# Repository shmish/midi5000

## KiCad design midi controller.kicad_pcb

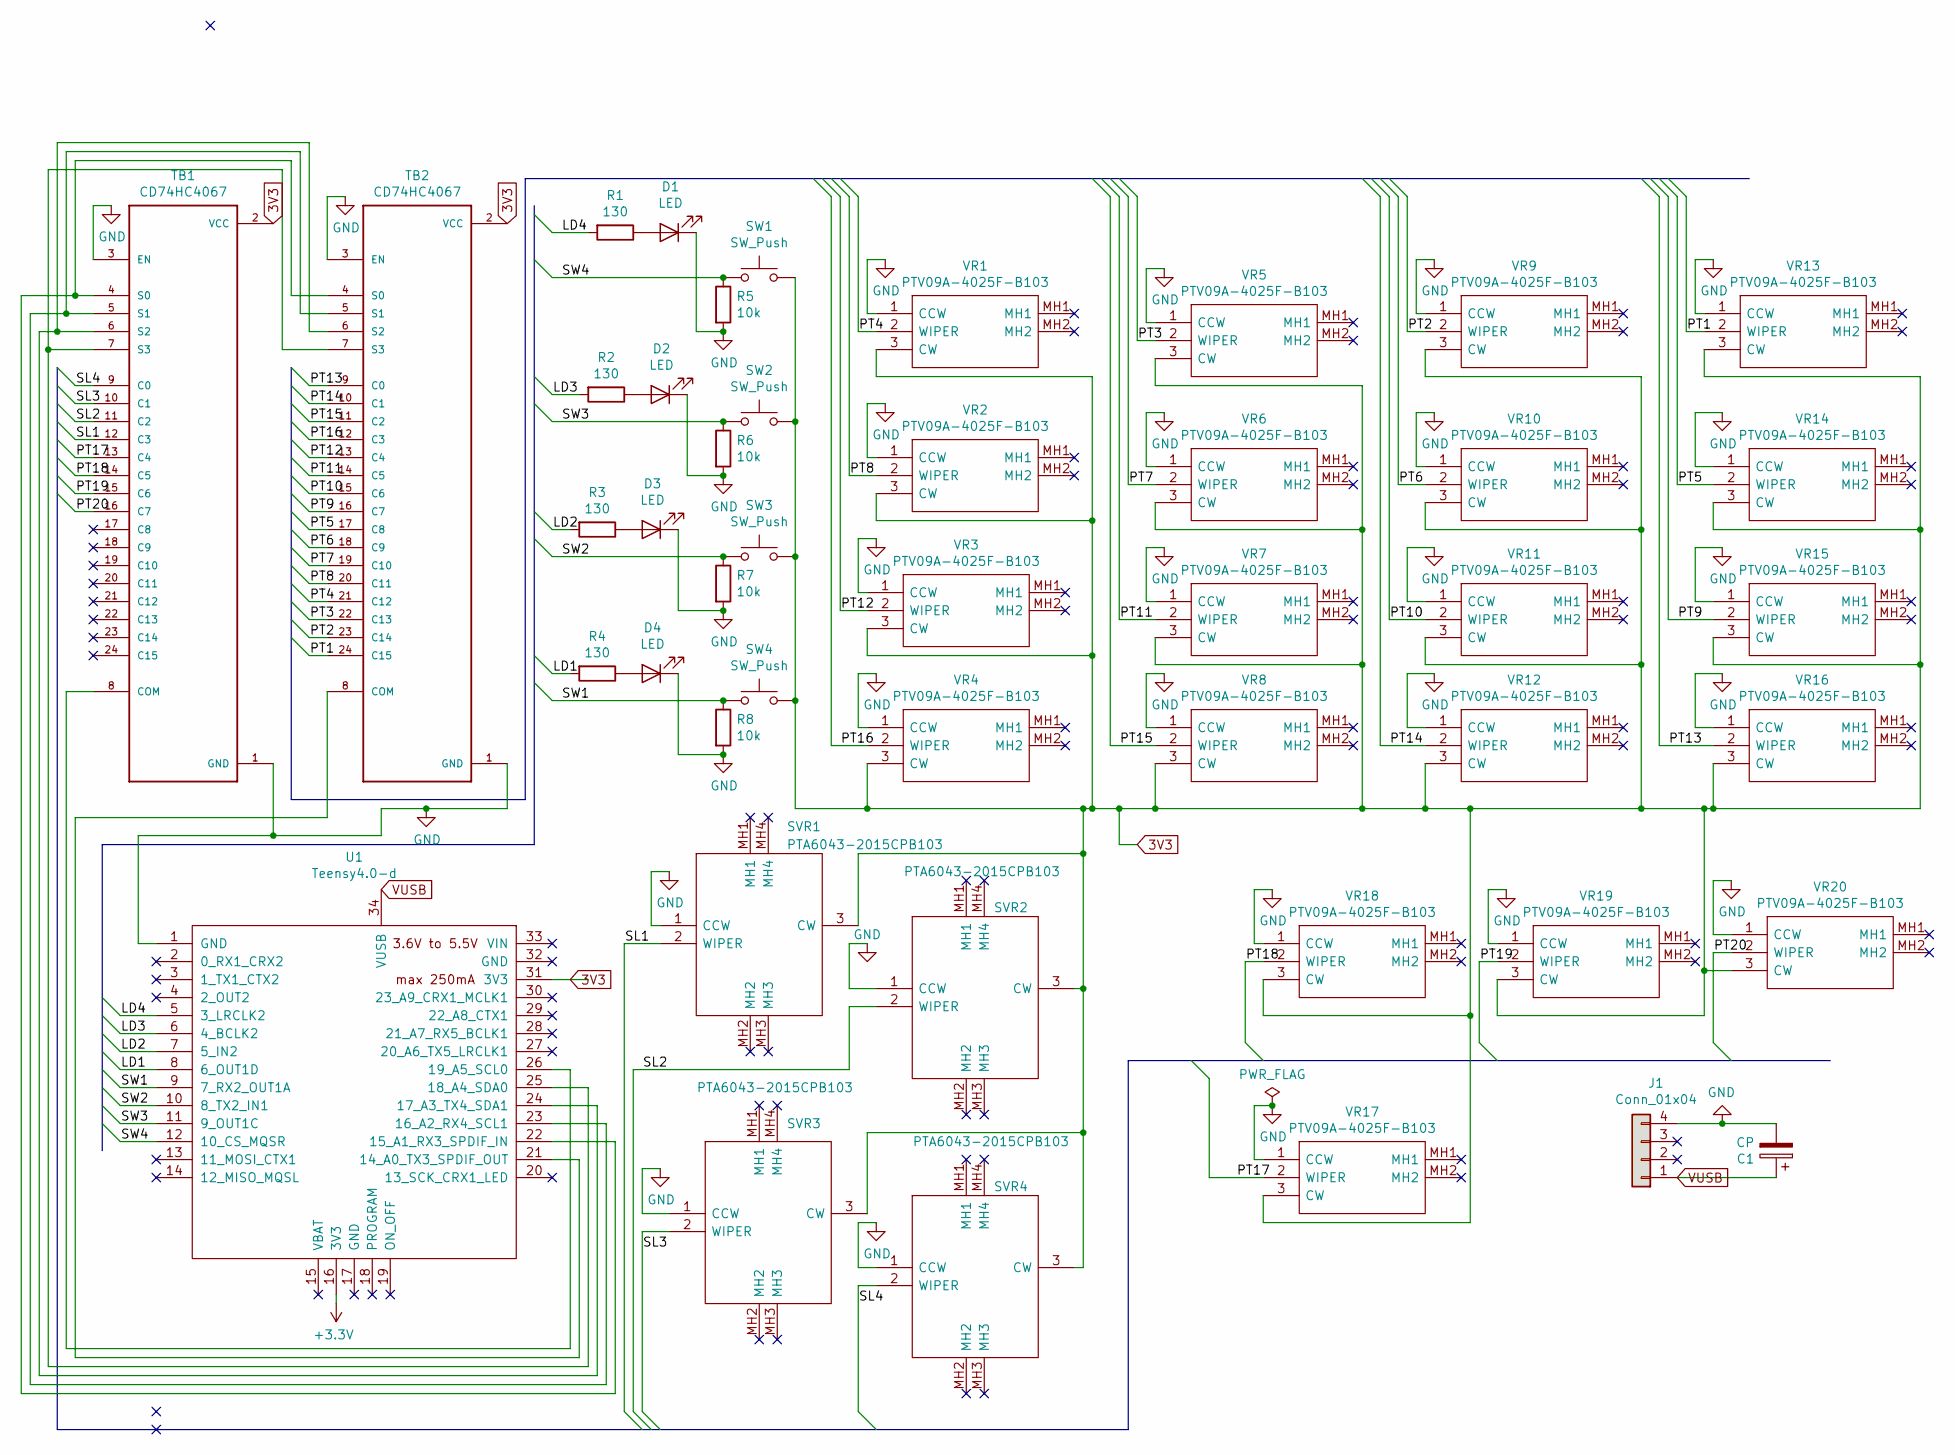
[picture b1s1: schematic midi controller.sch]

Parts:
C1: CP; C_Radial_D4.0mm_H7.0mm_P1.50mm
D1, D2, D3, D4: LED; LED_D5.0mm
J1: Conn_01x04; PinHeader_1x04_P2.54mm_Horizontal
R1, R2, R3, R4: 130; R_Axial_DIN0207_L6.3mm_D2.5mm_P7.62mm_Horizontal
R5, R6, R7, R8: 10k; R_Axial_DIN0207_L6.3mm_D2.5mm_P7.62mm_Horizontal
SVR1, SVR2, SVR3, SVR4: PTA6043-2015CPB103; PTA60432015CPB103; Mouser Part Number 652-PTA6432015CPB103
SW1, SW2, SW3, SW4: SW_Push; 800SP9B7M2QE
TB1, TB2: CD74HC4067; BOB-Mux
U1: Teensy4.0-d; Teensy40
VR1, VR2, VR3, VR4, VR5, VR6, VR7, VR8, VR9, VR10, VR11, VR12, VR13, VR14, VR15, VR16, VR17, VR18, VR19, VR20: PTV09A-4025F-B103; PTV09A4015FB103; Mouser Part Number 652-PTV09A-4025FB103

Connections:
3V3: SVR1.3 (CW), SVR2.3 (CW), SVR3.3 (CW), SVR4.3 (CW), SW1.2, SW2.2, SW3.2, SW4.2, TB1.2 (VCC), TB2.2 (VCC), U1.31 (3V3), VR1.3 (CW), VR2.3 (CW), VR3.3 (CW), VR4.3 (CW), VR5.3 (CW), VR6.3 (CW), VR7.3 (CW), VR8.3 (CW), VR9.3 (CW), VR10.3 (CW), VR11.3 (CW), VR12.3 (CW), VR13.3 (CW), VR14.3 (CW), VR15.3 (CW), VR16.3 (CW), VR17.3 (CW), VR18.3 (CW), VR19.3 (CW), VR20.3 (CW)
+3V3: U1.16 (3V3)
/LD1: R4.2, U1.8 (6_OUT1D)
/LD2: R3.2, U1.7 (5_IN2)
/LD3: R2.2, U1.6 (4_BCLK2)
/LD4: R1.2, U1.5 (3_LRCLK2)
/PT1: TB2.24 (C15), VR13.2 (WIPER)
/PT2: TB2.23 (C14), VR9.2 (WIPER)
/PT3: TB2.22 (C13), VR5.2 (WIPER)
/PT4: TB2.21 (C12), VR1.2 (WIPER)
/PT5: TB2.17 (C8), VR14.2 (WIPER)
/PT6: TB2.18 (C9), VR10.2 (WIPER)
/PT7: TB2.19 (C10), VR6.2 (WIPER)
/PT8: TB2.20 (C11), VR2.2 (WIPER)
/PT9: TB2.16 (C7), VR15.2 (WIPER)
/PT10: TB2.15 (C6), VR11.2 (WIPER)
/PT11: TB2.14 (C5), VR7.2 (WIPER)
/PT12: TB2.13 (C4), VR3.2 (WIPER)
/PT13: TB2.9 (C0), VR16.2 (WIPER)
/PT14: TB2.10 (C1), VR12.2 (WIPER)
/PT15: TB2.11 (C2), VR8.2 (WIPER)
/PT16: TB2.12 (C3), VR4.2 (WIPER)
/PT17: TB1.13 (C4), VR17.2 (WIPER)
/PT18: TB1.14 (C5), VR18.2 (WIPER)
/PT19: TB1.15 (C6), VR19.2 (WIPER)
/PT20: TB1.16 (C7), VR20.2 (WIPER)
/SL1: SVR1.2 (WIPER), TB1.12 (C3)
/SL2: SVR2.2 (WIPER), TB1.11 (C2)
/SL3: SVR3.2 (WIPER), TB1.10 (C1)
/SL4: SVR4.2 (WIPER), TB1.9 (C0)
/SW1: R8.1, SW4.1, U1.9 (7_RX2_OUT1A)
/SW2: R7.1, SW3.1, U1.10 (8_TX2_IN1)
/SW3: R6.1, SW2.1, U1.11 (9_OUT1C)
/SW4: R5.1, SW1.1, U1.12 (10_CS_MQSR)
GND: C1.2, D1.1 (K), D2.1 (K), D3.1 (K), D4.1 (K), J1.4, R5.2, R6.2, R7.2, R8.2, SVR1.1 (CCW), SVR2.1 (CCW), SVR3.1 (CCW), SVR4.1 (CCW), TB1.1 (GND), TB1.3 (EN), TB2.1 (GND), TB2.3 (EN), U1.1 (GND), VR1.1 (CCW), VR2.1 (CCW), VR3.1 (CCW), VR4.1 (CCW), VR5.1 (CCW), VR6.1 (CCW), VR7.1 (CCW), VR8.1 (CCW), VR9.1 (CCW), VR10.1 (CCW), VR11.1 (CCW), VR12.1 (CCW), VR13.1 (CCW), VR14.1 (CCW), VR15.1 (CCW), VR16.1 (CCW), VR17.1 (CCW), VR18.1 (CCW), VR19.1 (CCW), VR20.1 (CCW)
unnamed: D1.2 (A), R1.1
unnamed: D2.2 (A), R2.1
unnamed: D3.2 (A), R3.1
unnamed: D4.2 (A), R4.1
unnamed: TB1.4 (S0), TB2.4 (S0), U1.22 (15_A1_RX3_SPDIF_IN)
unnamed: TB1.5 (S1), TB2.5 (S1), U1.23 (16_A2_RX4_SCL1)
unnamed: TB1.6 (S2), TB2.6 (S2), U1.24 (17_A3_TX4_SDA1)
unnamed: TB1.7 (S3), TB2.7 (S3), U1.25 (18_A4_SDA0)
unnamed: TB1.8 (COM), U1.26 (19_A5_SCL0)
unnamed: TB2.8 (COM), U1.21 (14_A0_TX3_SPDIF_OUT)
VUSB: C1.1, J1.1, U1.34 (VUSB)

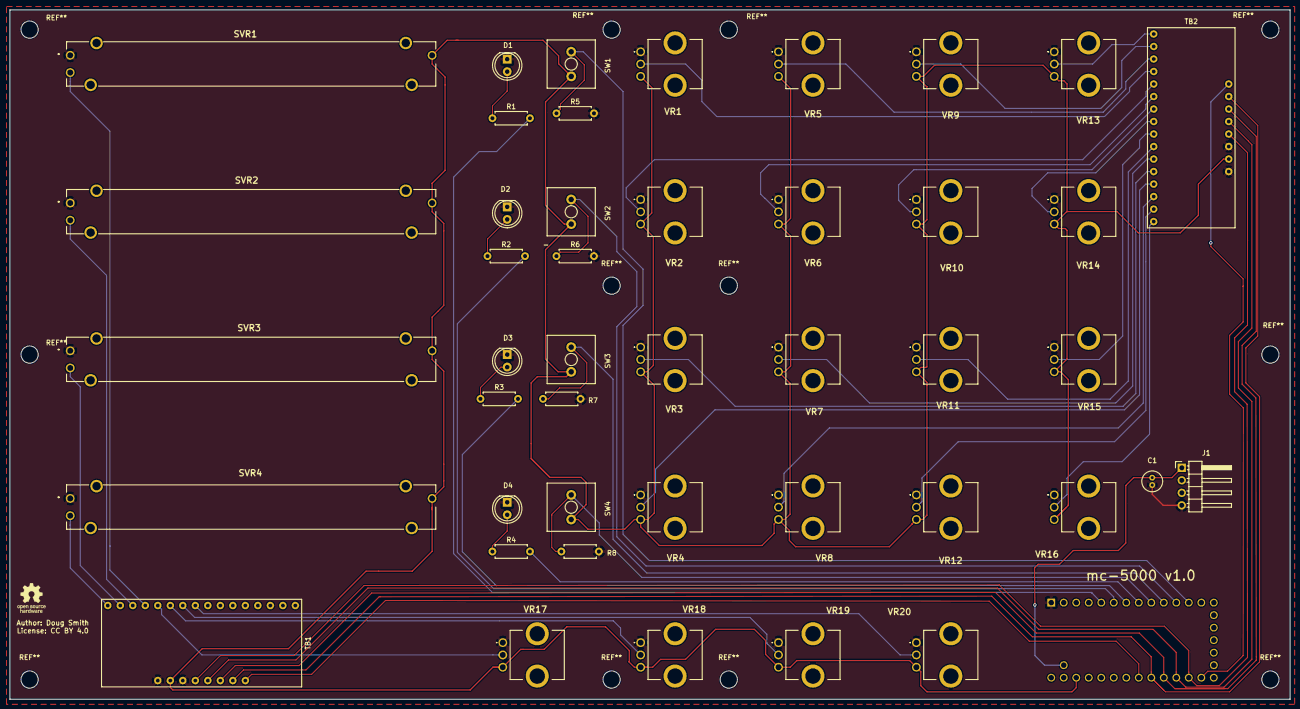
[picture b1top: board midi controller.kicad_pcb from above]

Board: 2 copper layers, 260.0 x 140.0 mm, 45 parts (1 on the bottom side), 45 nets.

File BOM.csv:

Bill of Materials,,,,,,,,
,,,,,,,,
Component,Qty,Value,Part,Description,Manufacturer,Vendor,unit price (C$),total
C1,1,100 nF,,Capacitor to smooth power start,,,,$1.00
"D1, D2, D3, D4",4,LED,,5mm red LED,,,,$1.00
J1,1,Conn_01x04,,4 pin Jumper header for USB power,,,,$1.00
"R1,2,3,4",4,130,,resistors for LED on 3V,,,,$1.00
"R5,6,7,8",4,10k,,resistors for pull-down switch,,,,$1.00
"SVR1,2,3,4",4,10k,RS6011SP6003,slide potentiometers,Alps,Mouser,$3.41,$13.64
"SW1,2,3,4",4,SW_Push,1543-650-149,SPST latch switch,Bourns,Mouser,$1.53,$6.12
VR1-20,20,10k,PTV09A-4025F-B103,rotary potentiometer,Bourns,Mouser,$1.05,$21.00
"TB1, 2",2,,CD74HC4067,16 channel multiplexer,Sparkfun,Lee's,$7.00,$14.00
U1,1,,Teensy 4.0,Teensy 4.0 with usb cable,PJRC,PJRC,$35.00,$35.00
PCB,1,,MIDI 5000,PCB,JLCPCB,JLCPCB,$30.00,$30.00
,,,,,,,,$124.76

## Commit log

2020-08-08 updated the fader and switch devices
2020-08-08 Added images

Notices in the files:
midi controller.kicad_pcb:
License: CC BY 4.0
midi controller.sch:
creativecommons.org/licenses/by/4.0
